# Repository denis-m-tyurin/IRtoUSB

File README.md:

# IRtoUSB
A device that emulates USB keyboard, receives commands from IR remote control and posts keyboard events to a host

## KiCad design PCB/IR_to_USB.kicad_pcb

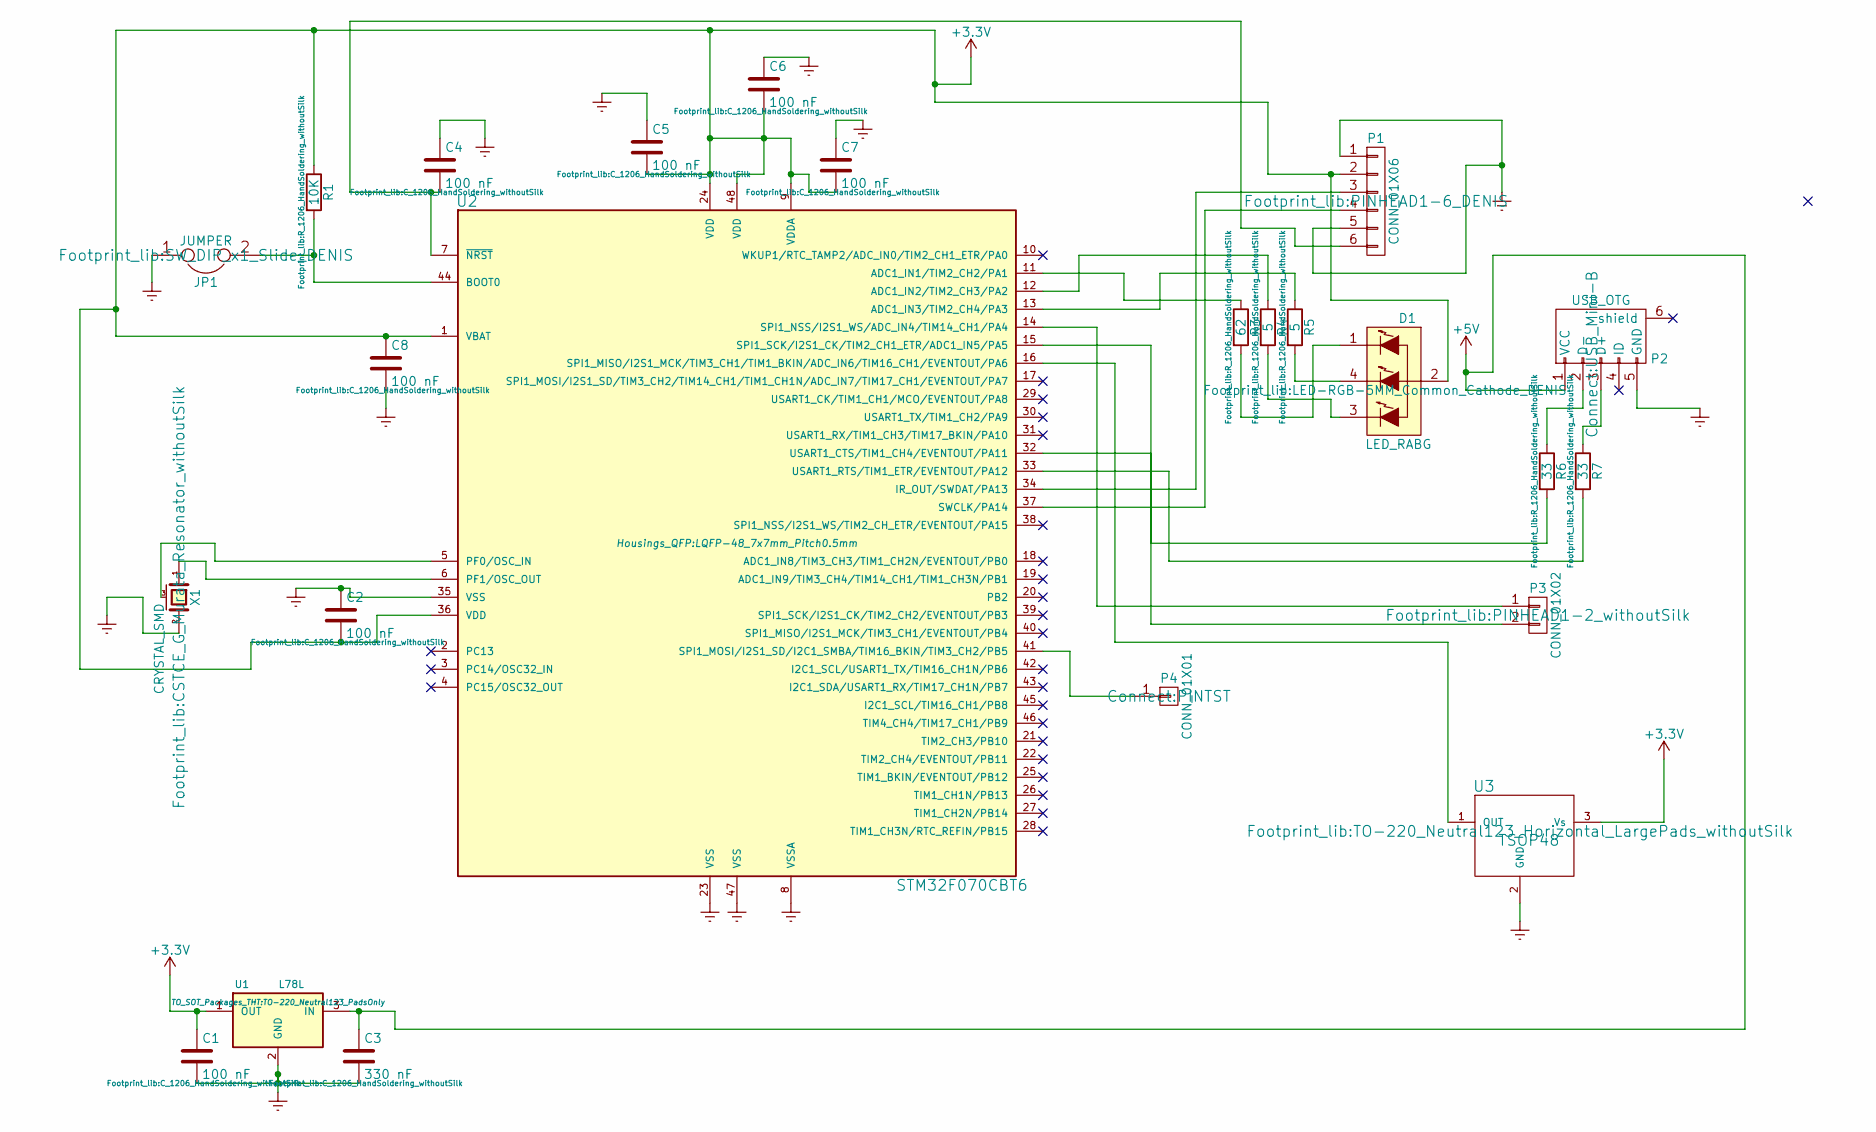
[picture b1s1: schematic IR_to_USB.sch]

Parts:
C1, C2, C4, C5, C6, C7, C8: 100 nF; C_1206_HandSoldering_withoutSilk
C3: 330 nF; C_1206_HandSoldering_withoutSilk
D1: LED_RABG; LED-RGB-5MM_Common_Cathode_DENIS
JP1: JUMPER; SW_DIP_x1_Slide_DENIS
P1: CONN_01X06; PINHEAD1-6_DENIS
P2: USB_OTG; USB_Mini-B
P3: CONN_01X02; PINHEAD1-2_withoutSilk
P4: CONN_01X01; PINTST
R1: 10K; R_1206_HandSoldering_withoutSilk
R3: 62; R_1206_HandSoldering_withoutSilk
R4, R5: 5; R_1206_HandSoldering_withoutSilk
R6, R7: 33; R_1206_HandSoldering_withoutSilk
U1: L78L; TO-220_Neutral123_PadsOnly
U2: STM32F070CBT6; LQFP-48_7x7mm_Pitch0.5mm
U3: TSOP48; TO-220_Neutral123_Horizontal_LargePads_withoutSilk
X1: CRYSTAL_SMD; CSTCE_G_Murata_Resonator_withoutSilk

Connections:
+3V3: C1.1, C2.2, C5.2, C6.2, C7.2, C8.1, D1.2 (COMMON_ANODE), P1.2, R1.1, U1.1 (OUT), U2.1 (VBAT), U2.9 (VDDA), U2.24 (VDD), U2.36 (VDD), U2.48 (VDD), U3.3 (Vs)
+5V: C3.1, P2.1 (VCC), U1.3 (IN)
Earth: C1.2, C2.1, C3.2, C4.1, C5.1, C6.1, C7.1, C8.2, JP1.1, P1.1, P1.5, P2.5 (GND), U1.2 (GND), U2.8 (VSSA), U2.23 (VSS), U2.35 (VSS), U2.47 (VSS), U3.2 (GND), X1.2
unnamed: C4.2, P1.6, U2.7 (~NRST)
unnamed: D1.1 (RED_CATHODE), R3.2
unnamed: D1.3 (BLUE_CATHODE), R4.2
unnamed: D1.4 (GREEN_CATHODE), R5.2
unnamed: JP1.2, R1.2, U2.44 (BOOT0)
unnamed: P1.3, U2.34 (IR_OUT/SWDAT/PA13)
unnamed: P1.4, U2.37 (SWCLK/PA14)
unnamed: P2.2 (D-), R6.1
unnamed: P2.3 (D+), R7.1
unnamed: P3.1, U2.14 (SPI1_NSS/I2S1_WS/ADC_IN4/TIM14_CH1/PA4)
unnamed: P3.2, U2.15 (SPI1_SCK/I2S1_CK/TIM2_CH1_ETR/ADC1_IN5/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)
unnamed: P4.1, U2.41 (SPI1_MOSI/I2S1_SD/I2C1_SMBA/TIM16_BKIN/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)
unnamed: R3.1, U2.11 (ADC1_IN1/TIM2_CH2/PA1)
unnamed: R4.1, U2.12 (ADC1_IN2/TIM2_CH3/PA2)
unnamed: R5.1, U2.13 (ADC1_IN3/TIM2_CH4/PA3)
unnamed: R6.2, U2.32 (USART1_CTS/TIM1_CH4/EVENTOUT/PA11)
unnamed: R7.2, U2.33 (USART1_RTS/TIM1_ETR/EVENTOUT/PA12)
unnamed: U2.5 (PF0/OSC_IN), X1.3 (case)
unnamed: U2.6 (PF1/OSC_OUT), X1.1
unnamed: U2.16 (SPI1_MISO/I2S1_MCK/TIM3_CH1/TIM1_BKIN/A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), U3.1 (OUT)

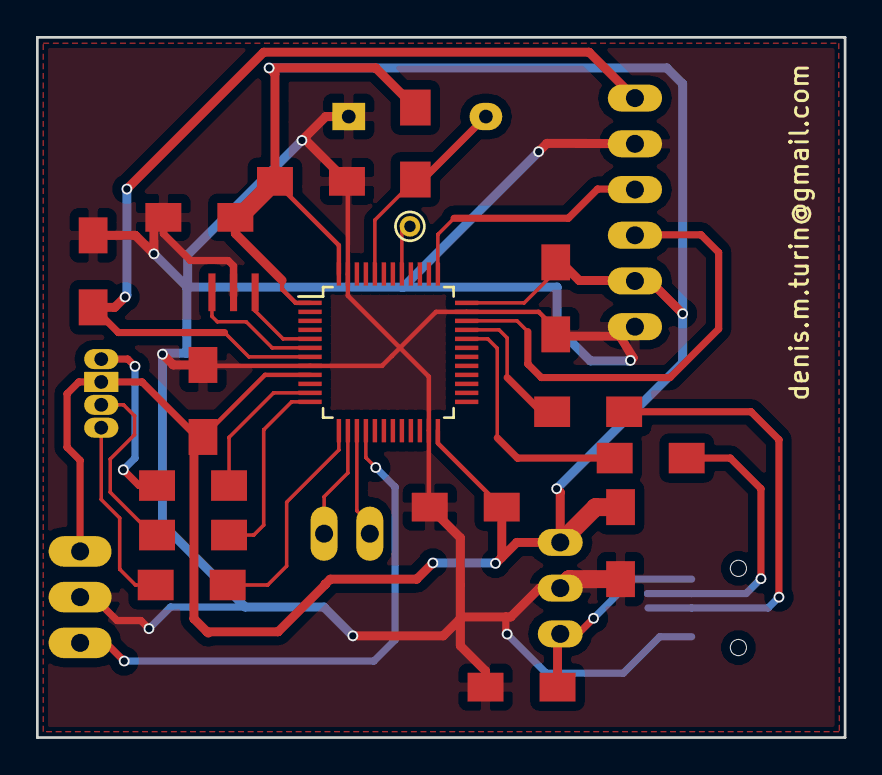
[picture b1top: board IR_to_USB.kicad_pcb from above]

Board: 2 copper layers, 44.9 x 38.9 mm, 24 parts (1 on the bottom side), 23 nets.

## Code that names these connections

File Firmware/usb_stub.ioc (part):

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Mcu.Name=STM32F070CBTx
Mcu.Package=LQFP48
Mcu.UserName=STM32F070CBTx
PA1.GPIOParameters=PinState
PA1.PinState=GPIO_PIN_SET
PA1.Signal=GPIO_Output
PA11.Mode=Device
PA11.Signal=USB_DM
PA12.Mode=Device
PA12.Signal=USB_DP
PA2.GPIOParameters=PinState
PA2.PinState=GPIO_PIN_SET
PA2.Signal=GPIO_Output
PA3.GPIOParameters=PinState
PA3.PinState=GPIO_PIN_SET
PA3.Signal=GPIO_Output
PA6.Signal=S_TIM3_CH1
PF0-OSC_IN.Mode=HSE-External-Oscillator
PF0-OSC_IN.Signal=RCC_OSC_IN
PF1-OSC_OUT.Mode=HSE-External-Oscillator
PF1-OSC_OUT.Signal=RCC_OSC_OUT
RCC.SYSCLKFreq_VALUE=48000000
RCC.SYSCLKSource=RCC_SYSCLKSOURCE_PLLCLK

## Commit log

2015-10-08 PCB first draft
2015-10-12 PCB in progress
2015-10-15 First PCB draft
2015-10-19 Rework PCB: changed RGB led type, removed reset button, etc.
2015-10-23 PCB ready
2015-12-15 Reworked PCB to double layers
2016-02-18 Initial firmware stub
2016-02-24 Remove stub firmware
2016-02-24 STM CubeMX stub
2016-05-18 Firmware stub
2017-05-15 Re-generated source project
2017-05-15 Basic working version: IR commands receiving and decoding - implemented USB Custom HID - implemented, but still has some problems with USB performance
2017-05-16 Fixed USB performance issue by increasing USB EP INT polling time to 4ms
